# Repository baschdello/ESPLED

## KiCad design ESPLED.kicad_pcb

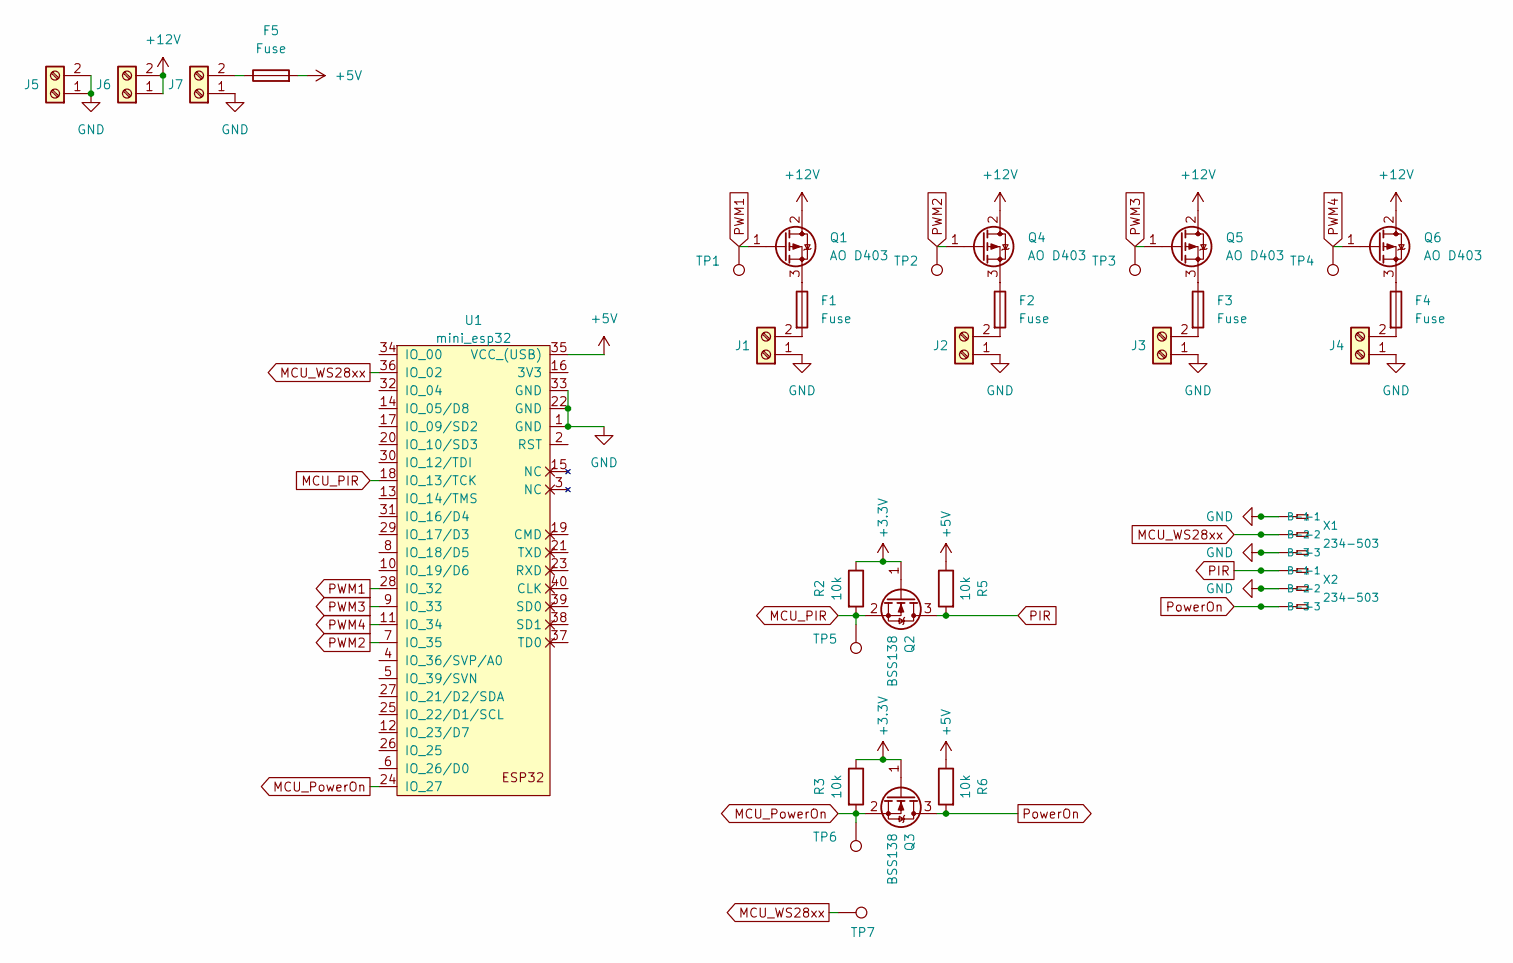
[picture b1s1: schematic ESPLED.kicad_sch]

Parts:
F1, F2, F3, F4, F5: Fuse; Fuseholder_Clip-5x20mm_Littelfuse_445-030_Inline_P20.50x5.2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
J1: PWM-1; TerminalBlock_MetzConnect_Type101_RT01602HBWC_1x02_P5.08mm_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
J2: PWM-2; TerminalBlock_MetzConnect_Type101_RT01602HBWC_1x02_P5.08mm_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
J3: PWM-3; TerminalBlock_MetzConnect_Type101_RT01602HBWC_1x02_P5.08mm_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
J4: PWM-4; TerminalBlock_MetzConnect_Type101_RT01602HBWC_1x02_P5.08mm_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
J5: GND; TerminalBlock_MetzConnect_Type101_RT01602HBWC_1x02_P5.08mm_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
J6: 12V; TerminalBlock_MetzConnect_Type101_RT01602HBWC_1x02_P5.08mm_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
J7: 5V-Stb; TerminalBlock_MetzConnect_Type101_RT01602HBWC_1x02_P5.08mm_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
Q1, Q4, Q5, Q6: AO D403; TO-252-2
Q2, Q3: BSS138; SOT-23
R2, R3, R5, R6: 10k; R_0805_2012Metric
TP1, TP2, TP3, TP4, TP5, TP6, TP7: TestPoint; PinHeader_1x01_P2.54mm_Vertical
U1: mini_esp32; ESP32_mini
X1, X2: 234-503; 233-503

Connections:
+3.3V: Q2.1 (G), Q3.1 (G), R2.1, R3.1
+5V: F5.2, R5.1, R6.1, U1.35 (VCC_(USB))
+12V: J6.1, J6.2, Q1.2 (D), Q4.2 (D), Q5.2 (D), Q6.2 (D)
GND: J1.1, J2.1, J3.1, J4.1, J5.1, J5.2, J7.1, U1.1 (GND), U1.22 (GND), U1.33 (GND), X1.A1 (-1), X1.A3 (-3), X1.B1 (B-1), X1.B3 (B-3), X2.A2 (-2), X2.B2 (B-2)
MCU_PIR: Q2.2 (S), R2.2, TP5.1, U1.18 (IO_13/TCK)
MCU_PowerOn: Q3.2 (S), R3.2, TP6.1, U1.24 (IO_27)
MCU_WS28xx: TP7.1, U1.36 (IO_02), X1.A2 (-2), X1.B2 (B-2)
unnamed: F1.2, J1.2
unnamed: F2.2, J2.2
unnamed: F3.2, J3.2
unnamed: F4.2, J4.2
unnamed: F5.1, J7.2
unnamed: F1.1, Q1.3 (S)
unnamed: F2.1, Q4.3 (S)
unnamed: F3.1, Q5.3 (S)
unnamed: F4.1, Q6.3 (S)
PIR: Q2.3 (D), R5.2, X2.A1 (-1), X2.B1 (B-1)
PWM1: Q1.1 (G), TP1.1, U1.28 (IO_32)
PWM2: Q4.1 (G), TP2.1, U1.7 (IO_35)
PWM3: Q5.1 (G), TP3.1, U1.9 (IO_33)
PWM4: Q6.1 (G), TP4.1, U1.11 (IO_34)
PowerOn: Q3.3 (D), R6.2, X2.A3 (-3), X2.B3 (B-3)

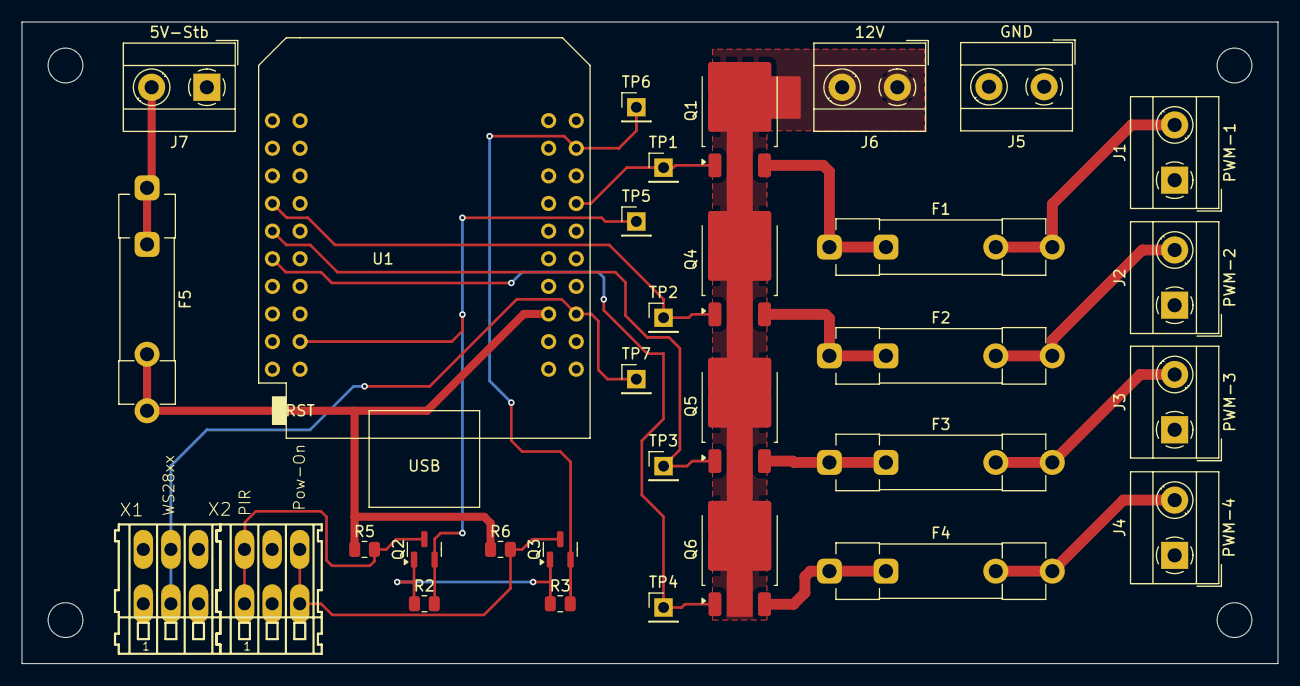
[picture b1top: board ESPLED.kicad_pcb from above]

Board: 2 copper layers, 115.5 x 59.0 mm, 32 parts (0 on the bottom side), 22 nets.

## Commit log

2025-01-09 Changed PIR from IO12 (strapping pin) to IO13
